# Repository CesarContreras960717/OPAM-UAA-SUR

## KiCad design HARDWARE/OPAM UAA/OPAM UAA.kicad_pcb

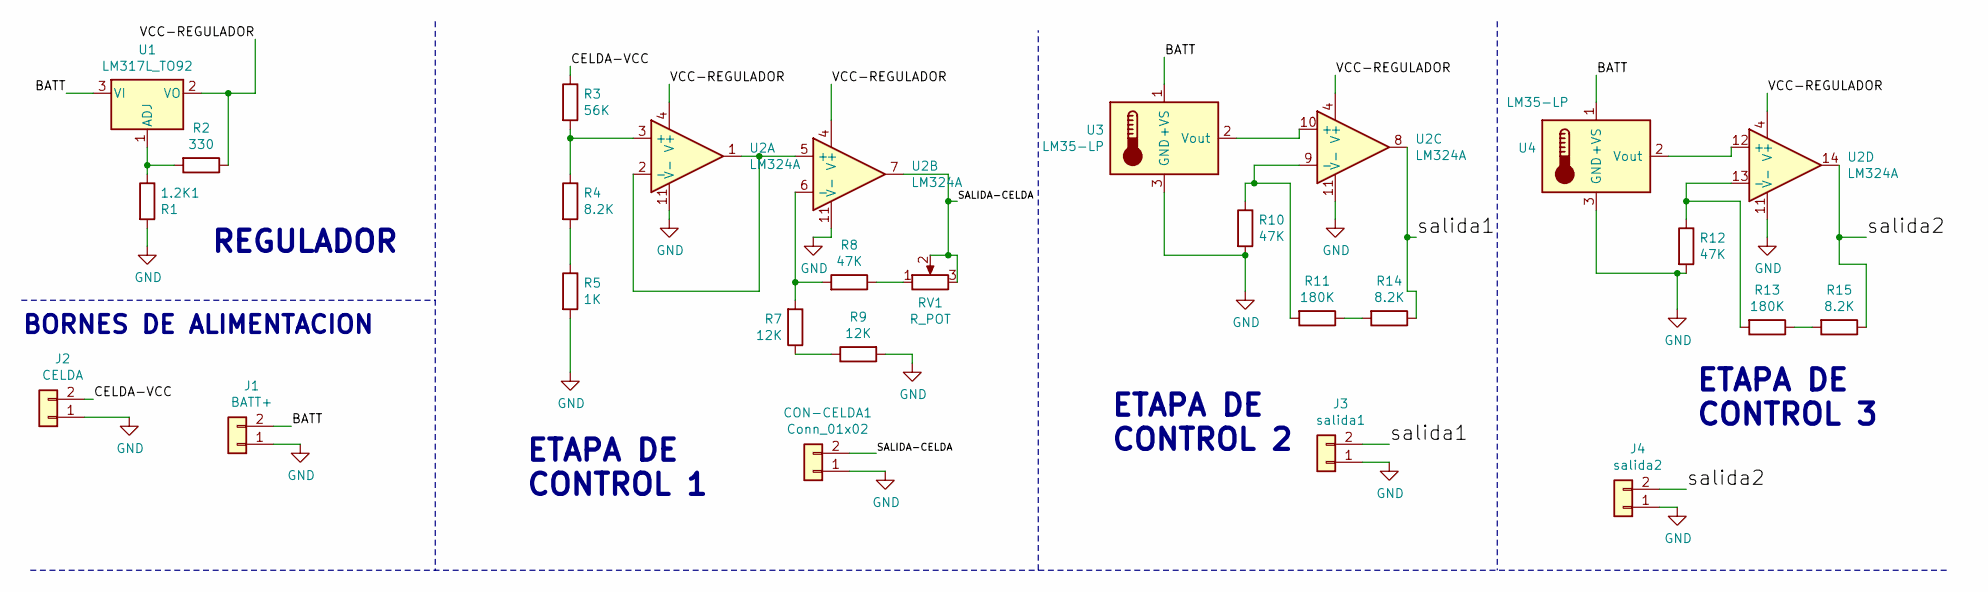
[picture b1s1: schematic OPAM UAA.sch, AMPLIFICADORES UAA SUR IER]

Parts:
1.2K1: R1; R_Axial_DIN0411_L9.9mm_D3.6mm_P12.70mm_Horizontal
CON-CELDA1: Conn_01x02; Pin_Header_Straight_1x02_Pitch2.54mm
J1: BATT+; Pin_Header_Straight_1x02_Pitch2.54mm
J2: CELDA; Pin_Header_Straight_1x02_Pitch2.54mm
J3: salida1; Pin_Header_Straight_1x02_Pitch2.54mm
J4: salida2; Pin_Header_Straight_1x02_Pitch2.54mm
R2: 330; R_Axial_DIN0411_L9.9mm_D3.6mm_P12.70mm_Horizontal
R3: 56K; R_Axial_DIN0411_L9.9mm_D3.6mm_P12.70mm_Horizontal
R4, R14, R15: 8.2K; R_Axial_DIN0411_L9.9mm_D3.6mm_P12.70mm_Horizontal
R5: 1K; R_Axial_DIN0411_L9.9mm_D3.6mm_P12.70mm_Horizontal
R7, R9: 12K; R_Axial_DIN0411_L9.9mm_D3.6mm_P12.70mm_Horizontal
R8, R10, R12: 47K; R_Axial_DIN0411_L9.9mm_D3.6mm_P12.70mm_Horizontal
R11, R13: 180K; R_Axial_DIN0411_L9.9mm_D3.6mm_P12.70mm_Horizontal
RV1: R_POT; Potentiometer_WirePads_largePads
U1: LM317L_TO92; TO-92_Inline_Wide
U2: LM324A; DIP-14_W7.62mm_Socket_LongPads
U3, U4: LM35-LP; TO-92_Inline_Narrow_Oval

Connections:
/BATT: J1.2, U1.3 (VI), U3.1 (+VS), U4.1 (+VS)
/CELDA-VCC: J2.2, R3.1
/SALIDA-CELDA: CON-CELDA1.2, RV1.2, RV1.3, U2.7
/VCC-REGULADOR: R2.1, U1.2 (VO), U2.4 (V+)
/salida1: J3.2, R14.1, U2.8
/salida2: J4.2, R15.1, U2.14
GND: 1.2K1.2, CON-CELDA1.1, J1.1, J2.1, J3.1, J4.1, R5.2, R9.2, R10.2, R12.2, U2.11 (V-), U3.3 (GND), U4.3 (GND)
unnamed: 1.2K1.1, R2.2, U1.1 (ADJ)
unnamed: R3.2, R4.1, U2.3 (+)
unnamed: R4.2, R5.1
unnamed: R7.1, R9.1
unnamed: R7.2, R8.2, U2.6 (-)
unnamed: R8.1, RV1.1
unnamed: R10.1, R11.2, U2.9 (-)
unnamed: R11.1, R14.2
unnamed: R12.1, R13.2, U2.13 (-)
unnamed: R13.1, R15.2
unnamed: U2.1, U2.2 (-), U2.5 (+)
unnamed: U2.10 (+), U3.2 (Vout)
unnamed: U2.12 (+), U4.2 (Vout)

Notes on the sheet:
REGULADOR
BORNES DE ALIMENTACION
ETAPA DE CONTROL 1
ETAPA DE CONTROL 2
ETAPA DE CONTROL 3

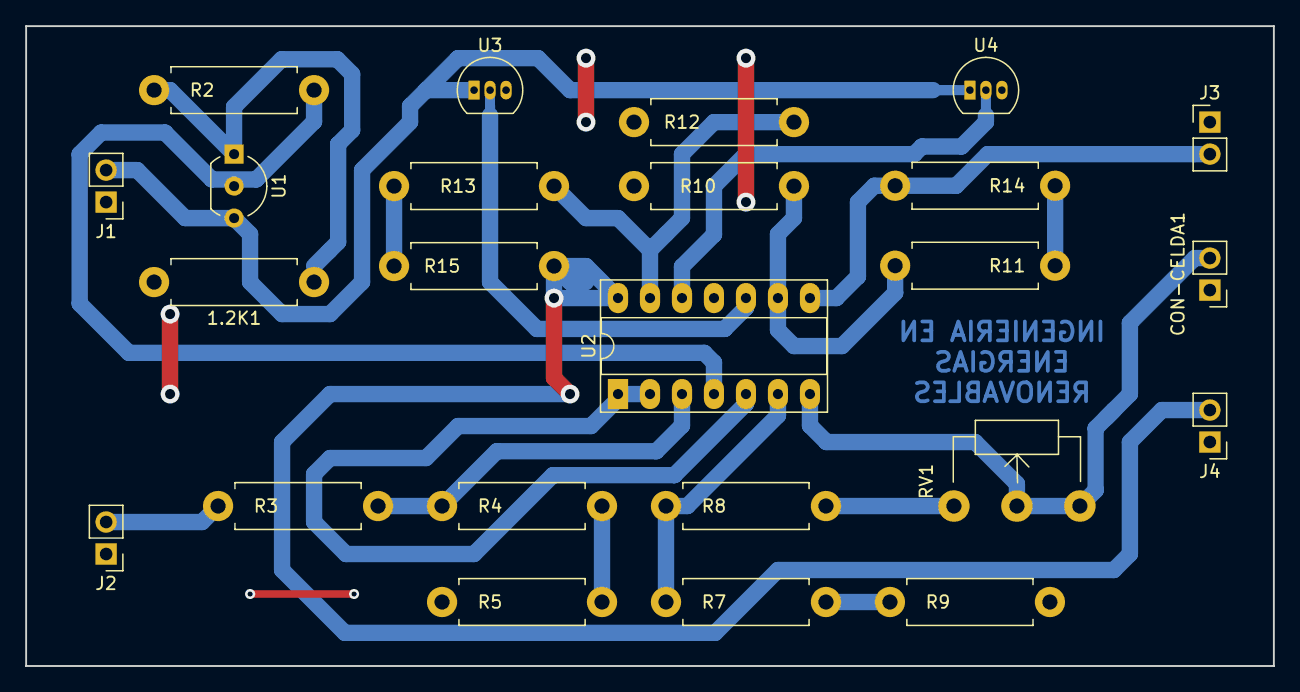
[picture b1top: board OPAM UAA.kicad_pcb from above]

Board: 2 copper layers, 99.1 x 50.8 mm, 24 parts (0 on the bottom side), 20 nets.

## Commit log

2019-06-17 SIMULACION
2019-06-17 schematic version 2.0
2019-06-17 PCB 2.0
2019-06-17 BUGS
2019-06-18 BUGS 2.0
2019-06-18 BUGS 3.0
2019-06-20 PCB 3.0
